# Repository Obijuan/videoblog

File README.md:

# videoblog
Recursos que menciono en el videoblog

* [Capítulos del 1 al 12: En wikirobots](http://www.iearobotics.com/wiki/index.php?title=Videoblog)
* [Nuevos capítulos (12 en adelante): En la wiki de github](https://github.com/Obijuan/videoblog/wiki)

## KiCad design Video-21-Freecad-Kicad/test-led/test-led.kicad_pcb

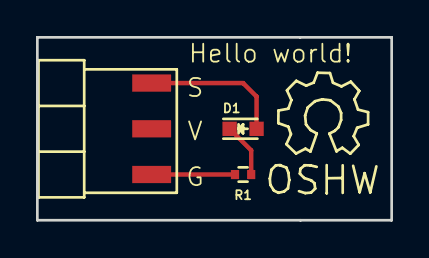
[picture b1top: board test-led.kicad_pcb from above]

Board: 2 copper layers, 19.7 x 10.2 mm, 4 parts (0 on the bottom side), 3 nets.

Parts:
D1: LED; LED_0603
DOC1: 1x3_pin_male_header_v_DOC; None
J1: 1x3_male_pin_Header_2.54mm; 1x3-pin-header-smd-right-angle
R1: 220R; R_0402

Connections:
GNDREF: J1.1, R1.2
unnamed: D1.A, J1.3
unnamed: D1.K, R1.1

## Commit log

2015-03-18 Video 3: openscad 2015.03
2015-03-19 VideoBlog 3: images added
2015-03-19 Small typos fixed
2015-03-29 Videoblog 4 images added
2015-03-29 Videoblog 5 images added
2015-03-29 Videoblog 6: images added
2015-03-29 Video 07: initial images
2015-04-02 2015-04-02-videoblog-7: images added
2015-04-02 Videoblog 8: Initial picture added. bq-E4_5-ubuntu-recovy.img added
2015-04-12 Videoblog 9: example python scripts added
2015-04-12 Videoblog 8: images added
2015-04-12 Videoblog 9: images added
2015-04-12 Videoblog 10: initial image added
2015-04-12 Images moved from videoblog 9 to 10
2015-04-12 Videoblog 11: initial image
2015-04-14 Videoblog 11: images added
2015-04-14 Robot of 3dof added
2015-04-14 videoblog 11: more images
2015-12-20 Video-12: counter example added
2015-12-20 [Video 12]: blank_bin: the counter that assign 0 to the leds
2015-12-20 [video 12]: El contador es parametrico
2015-12-20 [Video 12]: Initial image
2015-12-20 [Video 12]: icestick board image added
2015-12-21 Readme updated with the link to the github wiki
2015-12-21 [Video 12] Comments added to the counter
2015-12-21 [Video 12]: counter simulation screenshot
2015-12-24 [videoblog 12]: reset signal added to the gtkwave
2015-12-25 [videoblog 12]: Fixed typo (relog --> reloj). Thanks to Julio Olivenza
2016-01-23 Videoblog logo added
2016-01-23 Videoblog 13: initial commit
2016-03-12 Videoblog 17: examples
2016-03-19 Tut 18: sample carrier pictures
2016-03-19 Openlab samples carrier screenshot 1
2016-03-19 parametric container initial version
2016-03-19 Parametric-container initial design
2016-03-19 tut 18: final version of the parametric container
2016-03-19 Parametric container screenshot 1
2016-03-19 tut 18: Parametric container screenshot 2
2016-03-19 tut 18: Parametric container screenshot 3
2016-03-19 tut 18: Parametric container screenshot 4
2016-03-19 tut 18: Parametric container screenshot 5
2016-03-19 tut 18: Parametric container screenshot 6
2016-03-19 tut 18: Parametric container screenshot 7
2016-03-19 tut 18: Parametric container screenshot 8
2016-03-19 tut 18: Parametric container screenshot 9
2016-03-19 tut 18: Parametric container screenshot 10
2016-03-19 tut 18: Parametric container screenshots 11-15
2016-05-31 Videoblog 20: initial image
2016-05-31 kicad and oshw2 logos added
2016-05-31 Video 20: kicad screenshot 1
2016-05-31 Videoblog 20: kicad icezum schematics
2016-05-31 Videoblog 20: icezum schematics 3 screenshot
2016-05-31 Videoblog 20: kicad icon for center schematics
2016-05-31 videoblog 20: kicad icezum fpga sheet
2016-05-31 Videoblog 20: more kicad screenshots
2016-05-31 Videotutorial 20: inkscape screenshots
2016-06-24 Videoblog 21: test-led hello world board
2016-06-24 Videoblog 21: my led model added
2016-06-24 Videoblog 21: original led model added
2016-06-24 Videoblog 21: kicad screenshot
2016-06-24 Videoblog 21: Kicad schematic screenshot
2016-06-24 Videoblog 21: kicad pcb screenshot
2016-06-24 Videoblog 21: Kicad 3D viewer screenshot
2016-06-24 Videoblog 21: PCB example screenshot. Board body color changed
2016-06-24 Videoblog 21: More screenshots added
2016-06-24 Videoblog 21: More screenshots
2016-06-24 Videoblog 21: and more screenshots...
2016-07-28 Videoblog 22: icezum alhambra github wiki screenshot
2016-07-28 Videoblog 22: v1.0k release screenshot
2016-07-28 Videoblog 22: kicad schematics screenshots
2016-07-28 Videoblog 22: Kicad pcb screenshot 1
2016-07-28 Videoblog 22: Kicad pcb screenshots
2016-07-28 Videoblog 22: fixed in bug in the previous screenshot
2016-07-28 Videoblog 22: More pcb screenshots
2016-07-28 Videoblog 22: More screenshots
2016-07-28 Videoblog 22: Kicad 3D viewer screenshots
2016-07-28 Videoblog 22: Freecad screenshots
2016-07-29 Videoblog 22: Gerbview screenshots
2016-07-29 Videoblog 22: Inkscape screenshots
2016-07-29 Videoblog 22: Icezum Freecad screenshot
2016-07-29 Videoblog 22: Libreoffice screenshot
2017-07-03 chapter 26: picture and icestudio examples added
2017-07-03 Videoblog 26: more images added
2017-07-03 Videoblog 26: Example 1 Pulseview session added
2017-07-03 Videoblog 26: More images and examples added
2017-07-03 Videoblog 26: license added
2019-04-27 Videoblog 27: Images added
2019-04-27 Videoblog 27: image added
2019-04-29 videoblog 27: animation added
2019-04-29 videoblog 27: More animation added
2019-04-29 videoblog 27: More images added
2019-04-29 videoblog 27: old image removed
2019-04-29 Videoblog 27: more image added
2019-04-29 Videoblog 27: Example added
2019-04-30 Videoblog 27: Image updated
2019-05-01 Videoblog 27: Image upated
2019-05-01 VideoBlog 27: Image updted
2019-05-01 Videblog 27: Cover image added
2019-05-08 Videoblog 28: Image added
2019-05-08 Videoblog 28: Image and example added
2019-05-09 Videoblog 28: animation added
2019-05-11 Videoblog 28: Example 3 added
2019-05-11 Videoblog 28: Example 4 added
2019-05-11 Videoblog 28: Example 5 added
2019-05-11 Videoblog 28: More images added
2019-05-11 Videoblog 28: More animtion added
2019-05-12 Videoblog 28: images and examples added
2019-05-12 videoblog 28: cover image added
2019-05-12 Videoblog 28: Cover image updated!
2019-05-29 Videoblog 29: Conver image added
2019-05-29 Videoblog 29: Image added
2019-06-13 Videoblog 30: Image added
2019-06-13 Videoblog 30: Cover image added
2019-06-14 Videoblog 31: Cover image
2019-06-14 Videoblog 21: Cover image updated
2019-06-14 Videoblog 31: Cover image updated
2019-07-04 Videoblog 32: Cover image added
2019-07-04 Videoblog 32: Image updated
2019-07-04 Videoblog 33: Cover image added
2019-07-20 Videoblog 34: Image added
2019-07-20 Videoblog 34: Cover image added
2019-07-22 VideoBlog 35: Cover image added
2019-07-22 Videoblog 35: Cover image updated
2019-09-03 Video block 36: cover images added
2019-09-03 VideoBlog 36: Image added
2020-04-11 VideoBlog 37: Image added
2020-04-11 VB 27: Image added
2020-04-11 VB-27: Image added
2020-04-11 VB-27:Image added
2020-04-11 VB-27: j1a-cpu icestudio circuit added
2020-04-11 VB-27: Cover image added
2020-04-11 VB-27: .ice file updated
2020-05-22 VB-28: Cover image added
2020-05-23 VB-38: Cover image updated
2020-11-04 Videoblog 39: cover image added
2020-11-05 Videoblog 40: Cover image added
2020-11-05 videoblog 41: Cover image added
2020-11-05 Videoblog 42: cover image added
2020-11-05 Videoblog 43: Cover image added
2020-11-05 Videoblog 44: Cover image added
2021-04-07 Videoblog 45: Cover image added
2021-04-08 Videoblog 46: Cover image added
2021-04-13 Videoblog 47: Cover image added
2021-05-04 Video 48: Cover image added
2021-05-06 Video 49: Cover image added
2021-05-08 Videoblog 50: Cover image added
2021-05-09 Video 51: Cover image added
2021-05-31 Videoblog 52: cover image added
2021-05-31 video 52: Cover image updated
